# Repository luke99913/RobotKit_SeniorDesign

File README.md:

# RobotKit_SeniorDesign
 Senior Design Robot Kit and Controller for Introduction to Robotics Classes

The primary objective of this project was to redesign and manufacture a new robotics kit for use in the Introduction to Robotics class. The new kit is intended to fix the shortcomings of the old kit when it came to ease of use and reliability. Within the new kit the customer requested that a Raspberry Pi Pico be used, new DC motors with motor encoders are chosen, and the microcontroller should be Arduino IDE compatible. 

The secondary objective of this project was to design the robot with the intention of making a “Sumo Bot” demonstration for STEM outreach events. The plan was to have the robot kit have an onboard wireless connection that would talk with a developed controller. The controller would either be tilt or joystick activated and would drive the robot according to the direction inputted by the user. The body of the robot would also be capable of protecting the microcontroller as another robot crashed into it, attempting to push it out of the ring.  

 Software 

Software Design for Robot Vehicle (Acting as Wi-Fi Server) 

Introduction: This section outlines the design and functionality of the PicoW2 robot control program, which serves as a Wi-Fi server for remote control. The program is developed using the Arduino framework and facilitates robot movement based on input from a client. It covers the design aspects, dependencies, configurations, and initialization procedures of the robot control program. 

Dependencies: The program relies on the following libraries: 

WiFi.h: For handling Wi-Fi connectivity. 

LiquidCrystal_I2C.h: For interfacing with the LCD screen. 

Wire.h: For I2C communication. 

Configuration 

ai1, ai2, bi1, bi2: Pins for motor control. 

pwma, pwmb: PWM control pins for motor speed. 

lightSense: Pin for a light sensor. 

STASSID, STAPSK: Wifi network SSID(or IP) and password 

port: Port number for the server. 

Server Initialization 

Initializes a WiFi server on the specified port. 

Creates a structure (SentData) to hold data received from the client. 

Sets a default cooling motor voltage (motorCool). 

Setup Function 

Configures motor control pins, sets analog read resolution, and initializes the LCD. 

Configures WiFi settings and establishes a connection. 

Displays connection details on the serial monitor and LCD. 

Starts the server and displays server IP on the LCD for client use. 

Main Loop 

Resets motor control pins to LOW voltage. 

Checks for incoming client connections. 

If a client is connected, enters an infinite loop to receive and process data. 

Data Reception and Processing 

Reads data sent by the client into the currentData structure. 

Displays received data on the serial monitor and LCD. 

Controls motor movement based on received data. 

Movement Control Functions  

Forwards: 

Controls forward movement upon receiving a positive Y value. 

The Y value also controls the overall speed of the motors. 

Adjusts motor speed to change direction based on the X value.

Backwards: 

Controls backward movement upon receiving a negative Y value. 

The Y value also controls the overall speed of the motors. 

Adjusts motor speed to change direction based on the X value. 

Spin: 

Controls spinning movement upon receiving a zero Y value. 

Adjusts motor speed and direction based on the sign and value of X. 

Conclusion The program successfully establishes a WiFi server, receives input from a client, and controls the robot's movement based on the received data. The movement is determined by the X and Y values, with different functions for forward, backward, and spinning motions. The LCD screen provides status updates, and the serial monitor logs relevant information. 

Note The specific functionalities related to the light sensor and an unspecified button are mentioned in the code but commented out. These functionalities can be troubleshooted and integrated into the sumo bot program. 

Software Design for Remote Control (Acts as WiFi Client) 

Introduction: This section provides a detailed overview of the software design for the Arduino program responsible for remote controlling the robot. The program reads sensor data from an MPU6050 sensor, potentiometer, and joystick, establishing a WiFi connection to send the data to the server (Robot Kit). It covers key components, data structures, code structure, and dependencies for the remote-control program. 

Dependencies: 

WiFi.h: For handling WiFi connectivity. 

Adafruit_MPU6050.h: For handling the Accelrometer/gyro 

Adafruit_Sensor.h: For handling sensor readings 

Wire.h: For I2C communication. 

Key Components  

MPU6050 Sensor - Reads accelerometer data with custom I2C pins. 2.2.2 

Joystick - Reads analog data from two joystick pins. - Used to control sensor data if activated.  

WiFi Connection - Uses Pico W WiFi module for connecting to a WiFi network.  

Potentiometer - Reads analog data from a potentiometer. - Controls the magnitude of sensor data. 

Configuration 

I2C_SDA, I2C_SCL: For MPU-6050 communication 

STASSID, STAPSK: Wifi network SSID(or IP) and password  

host, port: server identified by IP address and port. - Sends sensor data to the server. 

potPin: For potentiometer communication 

Communicated Data Structure 

A structure named SentData stores sensor data, including X and Y values and the potentiometer value to send to the Robot over the wifi network. 

Setup Function: 

Pin Initialization - Configures default LED pin and custom I2C pins. 

Serial Communication - Initializes serial communication for debugging. 

MPU6050 Initialization - Initializes the MPU6050 sensor with specific ranges and bandwidth.  

WiFi Connection - Connects to the WiFi network using provided credentials. - Reboots if connection fails. 

Main Loop: 

Client Initialization - Initializes a new WiFi client for server communication.  

SentData Initialization - Initializes the currentData struct used for data communication. 

Sensor Data Collection - Reads potentiometer value and checks for joystick activation. - Reads accelerometer data if joystick is not activated. Reads joystick values if joystick is activated.  

Data Normalization - Normalizes pitch and roll values considering dead zones and maximum angles or normalizes joystick values considering just dead zones. - Multiplies normalized values by the potentiometer value and loads the values into the currentData struct.  

Data Transmission - Sends the entire SentData structure named currentData to the server. 

Conclusion This section provides an in-depth understanding of the software design for the Arduino program. It covers key components, data structures, code structure, and dependencies. Developers can use this document as a reference for maintenance and future enhancements.

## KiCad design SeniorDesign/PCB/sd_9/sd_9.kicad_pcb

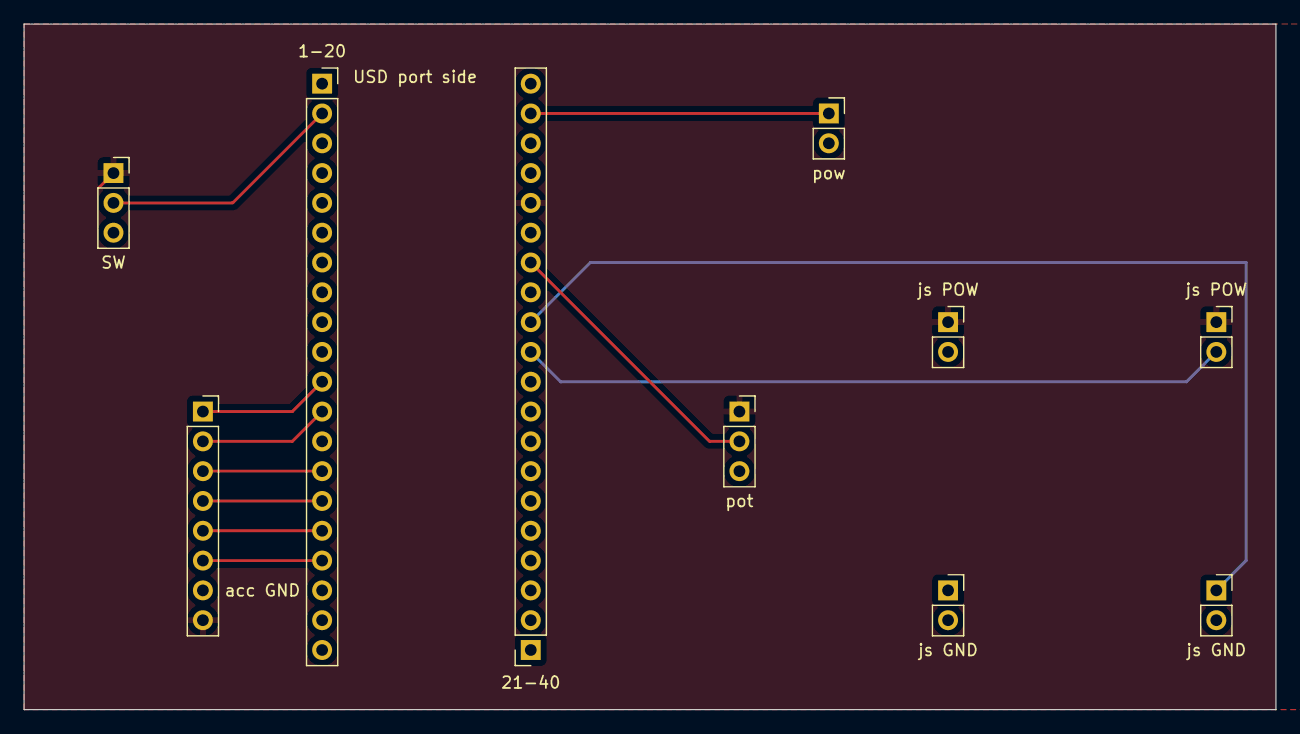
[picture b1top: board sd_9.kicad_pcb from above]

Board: 2 copper layers, 106.7 x 58.4 mm, 10 parts (0 on the bottom side), 13 nets.

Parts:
1-20, 21-40: Conn_01x20_Socket; PinSocket_1x20_P2.54mm_Vertical
SW: Conn_01x03_Socket; PinSocket_1x03_P2.54mm_Vertical
acc GND: Conn_01x08_Socket; PinSocket_1x08_P2.54mm_Vertical
js GND: Conn_01x02_Socket; PinSocket_1x02_P2.54mm_Vertical
js GND#2: Conn_01x02_Socket; PinSocket_1x02_P2.54mm_Vertical
js POW: Conn_01x02_Socket; PinSocket_1x02_P2.54mm_Vertical
js POW#2: Conn_01x02_Socket; PinSocket_1x02_P2.54mm_Vertical
pot: Conn_01x03_Socket; PinSocket_1x03_P2.54mm_Vertical
pow: Conn_01x02_Socket; PinSocket_1x02_P2.54mm_Vertical

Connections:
+3.3V: 21-40.16, SW.1, acc GND.8, js POW.1, js POW#2.1, pot.1
GND: 1-20.3, 1-20.8, 1-20.13, 1-20.18, 21-40.3, 21-40.8, 21-40.13, 21-40.18, SW.3, acc GND.7, js GND.2, js GND#2.2, pot.3, pow.2
unnamed: 1-20.11, acc GND.1
unnamed: 1-20.12, acc GND.2
unnamed: 1-20.14, acc GND.3
unnamed: 1-20.15, acc GND.4
unnamed: 1-20.16, acc GND.5
unnamed: 1-20.17, acc GND.6
unnamed: 1-20.2, SW.2
unnamed: 21-40.14, pot.2
unnamed: 21-40.19, pow.1
unnamed: 21-40.11, js POW#2.2
unnamed: 21-40.12, js GND#2.1

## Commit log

2023-12-14 Initial File Dump
    Date: 12-13-2023
2023-12-14 Updated README
    Date: 12-13-2023
